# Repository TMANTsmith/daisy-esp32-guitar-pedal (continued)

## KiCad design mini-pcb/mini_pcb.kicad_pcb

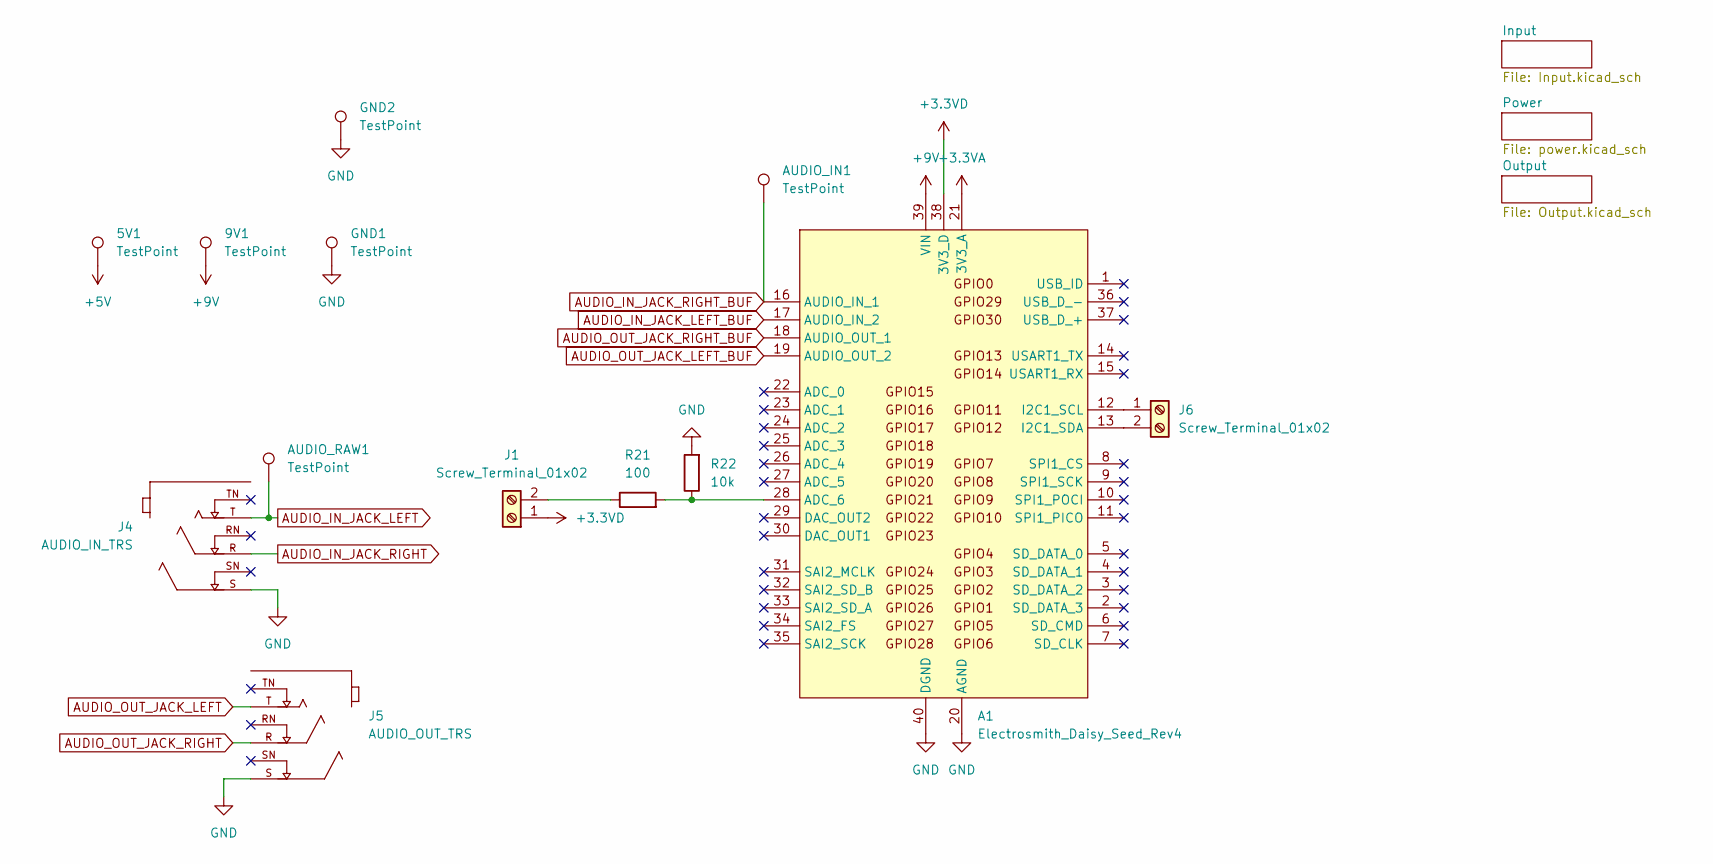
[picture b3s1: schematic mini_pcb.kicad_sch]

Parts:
5V1, 9V1: TestPoint; TestPoint_Pad_D2.0mm
A1: Electrosmith_Daisy_Seed_Rev4; Electrosmith_Daisy_Seed; MPN C50984
AUDIO_IN1: TestPoint; TestPoint_Pad_D2.0mm
AUDIO_RAW1: TestPoint; TestPoint_Pad_D2.0mm
GND1, GND2: TestPoint; TestPoint_Pad_D2.0mm
J1, J6: Screw_Terminal_01x02; TerminalBlock_Xinya_XY308-2.54-2P_1x02_P2.54mm_Horizontal; MPN C8465
J4: AUDIO_IN_TRS; Jack_6.35mm_Neutrik_NMJ6HCD3_Horizontal; PARTREV 26.02.2021
J5: AUDIO_OUT_TRS; Jack_6.35mm_Neutrik_NMJ6HCD3_Horizontal; PARTREV 26.02.2021
R21: 100; R_0603_1608Metric; MPN C22775
R22: 10k; R_0603_1608Metric; MPN C25804

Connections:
+3.3VA: A1.21 (3V3_A)
+3.3VD: A1.38 (3V3_D), J1.1
+5V: 5V1.1 (1_1); also elsewhere on the board
+9V: 9V1.1 (1_1), A1.39 (VIN); also elsewhere on the board
AUDIO_IN_JACK_LEFT: AUDIO_RAW1.1 (1_1), J4.T; also elsewhere on the board
AUDIO_IN_JACK_LEFT_BUF: A1.17 (AUDIO_IN_2); also elsewhere on the board
AUDIO_IN_JACK_RIGHT: J4.R; also elsewhere on the board
AUDIO_IN_JACK_RIGHT_BUF: A1.16 (AUDIO_IN_1), AUDIO_IN1.1 (1_1); also elsewhere on the board
AUDIO_OUT_JACK_LEFT: J5.T; also elsewhere on the board
AUDIO_OUT_JACK_LEFT_BUF: A1.19 (AUDIO_OUT_2); also elsewhere on the board
AUDIO_OUT_JACK_RIGHT: J5.R; also elsewhere on the board
AUDIO_OUT_JACK_RIGHT_BUF: A1.18 (AUDIO_OUT_1); also elsewhere on the board
GND: A1.20 (AGND), A1.40 (DGND), GND1.1 (1_1), GND2.1 (1_1), J4.S, J5.S, R22.2; also elsewhere on the board
unnamed: A1.28 (ADC_6), R21.2, R22.1
unnamed: A1.12 (I2C1_SCL), J6.1
unnamed: A1.13 (I2C1_SDA), J6.2
unnamed: J1.2, R21.1

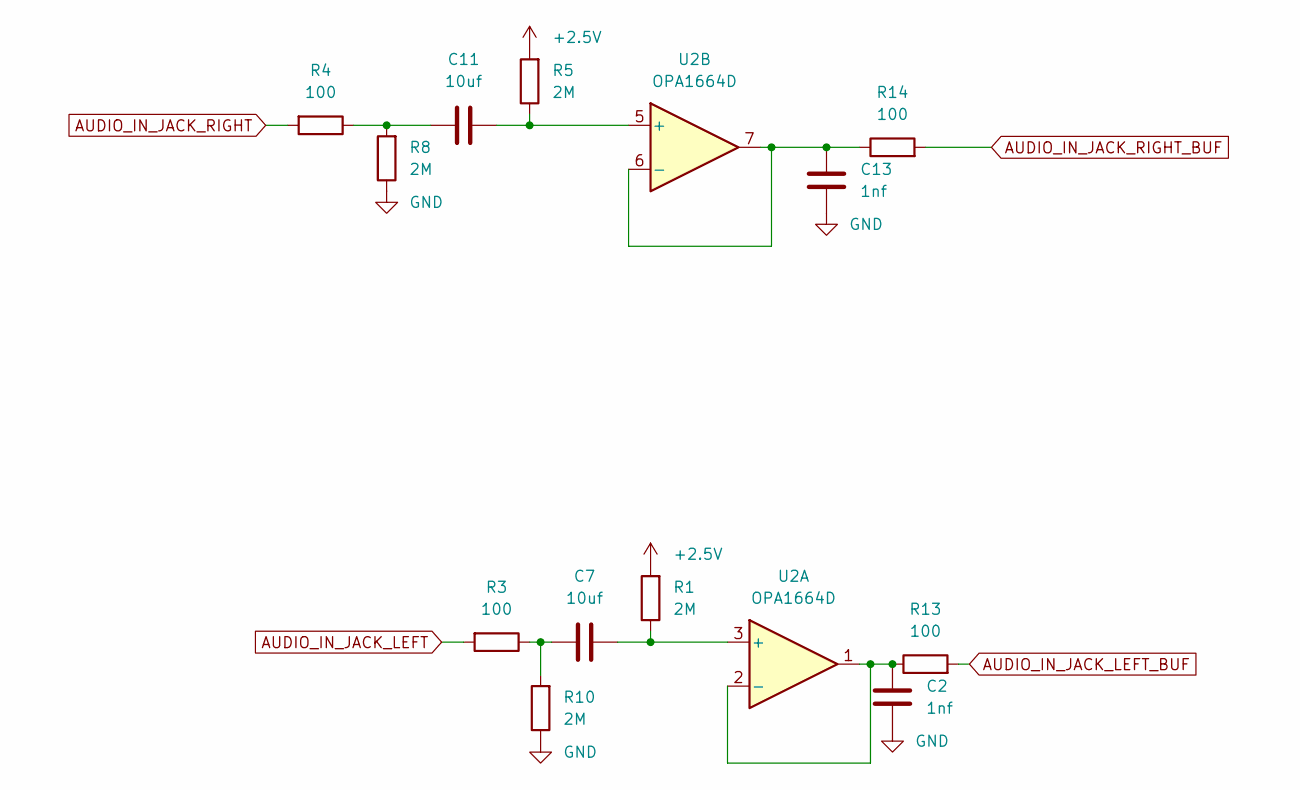
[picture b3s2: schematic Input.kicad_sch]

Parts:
C2, C13: 1nf; C_0805_2012Metric; MPN C46653
C7, C11: 10uf; C_0805_2012Metric; MPN C440198
R1, R5, R8, R10: 2M; R_0603_1608Metric; MPN C22976
R3, R4, R13, R14: 100; R_0603_1608Metric; MPN C22775
U2: OPA1664D; SOIC-14_3.9x8.7mm_P1.27mm; MPN C69414

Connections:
+2.5V: R1.2, R5.2; also elsewhere on the board
AUDIO_IN_JACK_LEFT: R3.2; also elsewhere on the board
AUDIO_IN_JACK_LEFT_BUF: R13.2; also elsewhere on the board
AUDIO_IN_JACK_RIGHT: R4.2; also elsewhere on the board
AUDIO_IN_JACK_RIGHT_BUF: R14.2; also elsewhere on the board
GND: C2.1, C13.1, R8.1, R10.1; also elsewhere on the board
unnamed: C7.1, R3.1, R10.2
unnamed: C11.1, R4.1, R8.2
unnamed: C7.2, R1.1, U2.3 (+)
unnamed: C2.2, R13.1, U2.1, U2.2 (-)
unnamed: C11.2, R5.1, U2.5 (+)
unnamed: C13.2, R14.1, U2.6 (-), U2.7

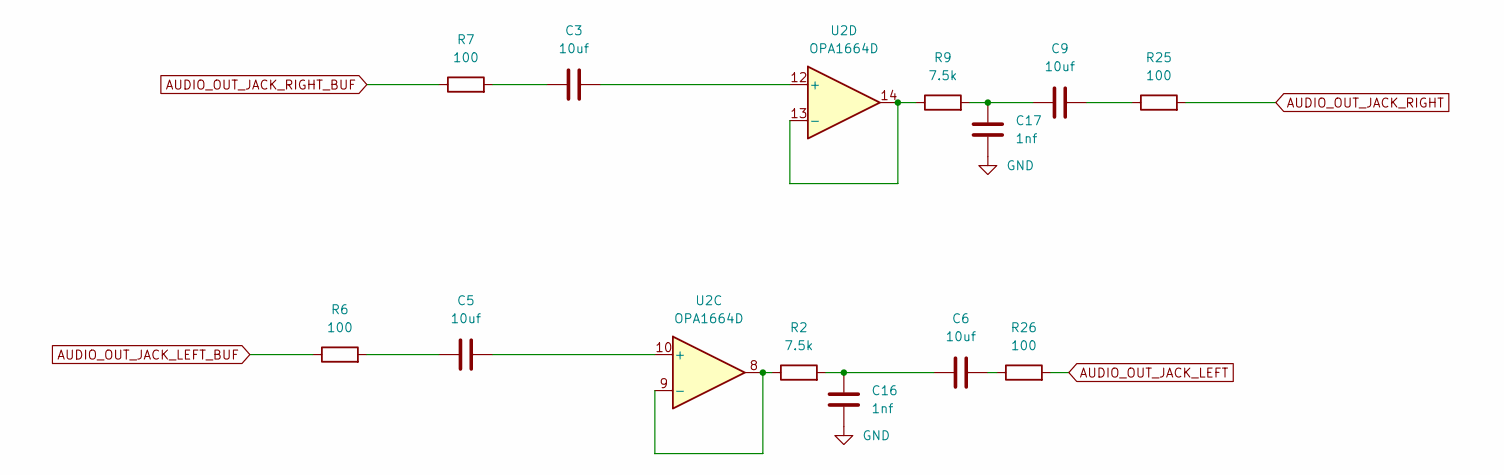
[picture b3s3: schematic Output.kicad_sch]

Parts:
C3, C5, C6, C9: 10uf; C_0805_2012Metric; MPN C440198
C16, C17: 1nf; C_0805_2012Metric; MPN C46653
R2, R9: 7.5k; R_0603_1608Metric; MPN C23234
R6, R7, R25, R26: 100; R_0603_1608Metric; MPN C22775
U2: OPA1664D; SOIC-14_3.9x8.7mm_P1.27mm; MPN C69414

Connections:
AUDIO_OUT_JACK_LEFT: R26.2; also elsewhere on the board
AUDIO_OUT_JACK_LEFT_BUF: R6.1; also elsewhere on the board
AUDIO_OUT_JACK_RIGHT: R25.2; also elsewhere on the board
AUDIO_OUT_JACK_RIGHT_BUF: R7.1; also elsewhere on the board
GND: C16.1, C17.1; also elsewhere on the board
unnamed: C3.1, R7.2
unnamed: C5.1, R6.2
unnamed: C6.2, R26.1
unnamed: C9.2, R25.1
unnamed: C6.1, C16.2, R2.2
unnamed: C9.1, C17.2, R9.2
unnamed: C5.2, U2.10 (+)
unnamed: R2.1, U2.8, U2.9 (-)
unnamed: C3.2, U2.12 (+)
unnamed: R9.1, U2.13 (-), U2.14

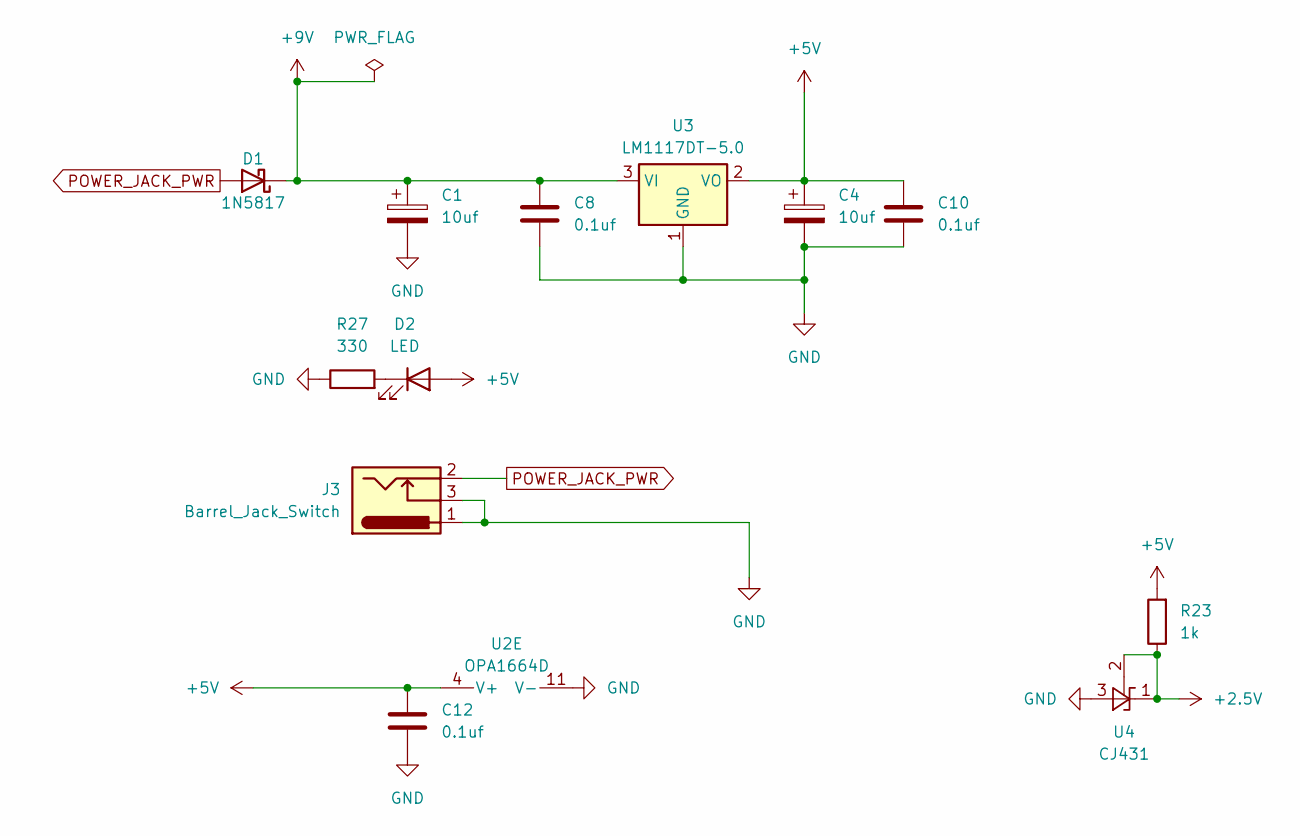
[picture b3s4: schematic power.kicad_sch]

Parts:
C1, C4: 10uf; CP_EIA-3216-18_Kemet-A; MPN C7171
C8, C10, C12: 0.1uf; C_0805_2012Metric; MPN C49678
D1: 1N5817; D_SOD-123; MPN C8598
D2: LED; LED_0805_2012Metric; MPN C2297
J3: Barrel_Jack_Switch; BarrelJack_Horizontal; MPN C16214
R23: 1k; R_0603_1608Metric; MPN C21190
R27: 330; R_0603_1608Metric; MPN C23138
U2: OPA1664D; SOIC-14_3.9x8.7mm_P1.27mm; MPN C69414
U3: LM1117DT-5.0; TO-252-2; MPN C354068
U4: CJ431; SOT-23-3; MPN C21190

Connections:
+2.5V: R23.1, U4.1 (FB), U4.2 (K); also elsewhere on the board
+5V: C4.1, C10.1, C12.1, D2.2 (A), R23.2, U2.4 (V+), U3.2 (VO); also elsewhere on the board
+9V: C1.1, C8.1, D1.1 (K), U3.3 (VI); also elsewhere on the board
GND: C1.2, C4.2, C8.2, C10.2, C12.2, J3.1, J3.3, R27.1, U2.11 (V-), U3.1 (GND), U4.3 (A); also elsewhere on the board
unnamed: D2.1 (K), R27.2
POWER_JACK_PWR: D1.2 (A), J3.2

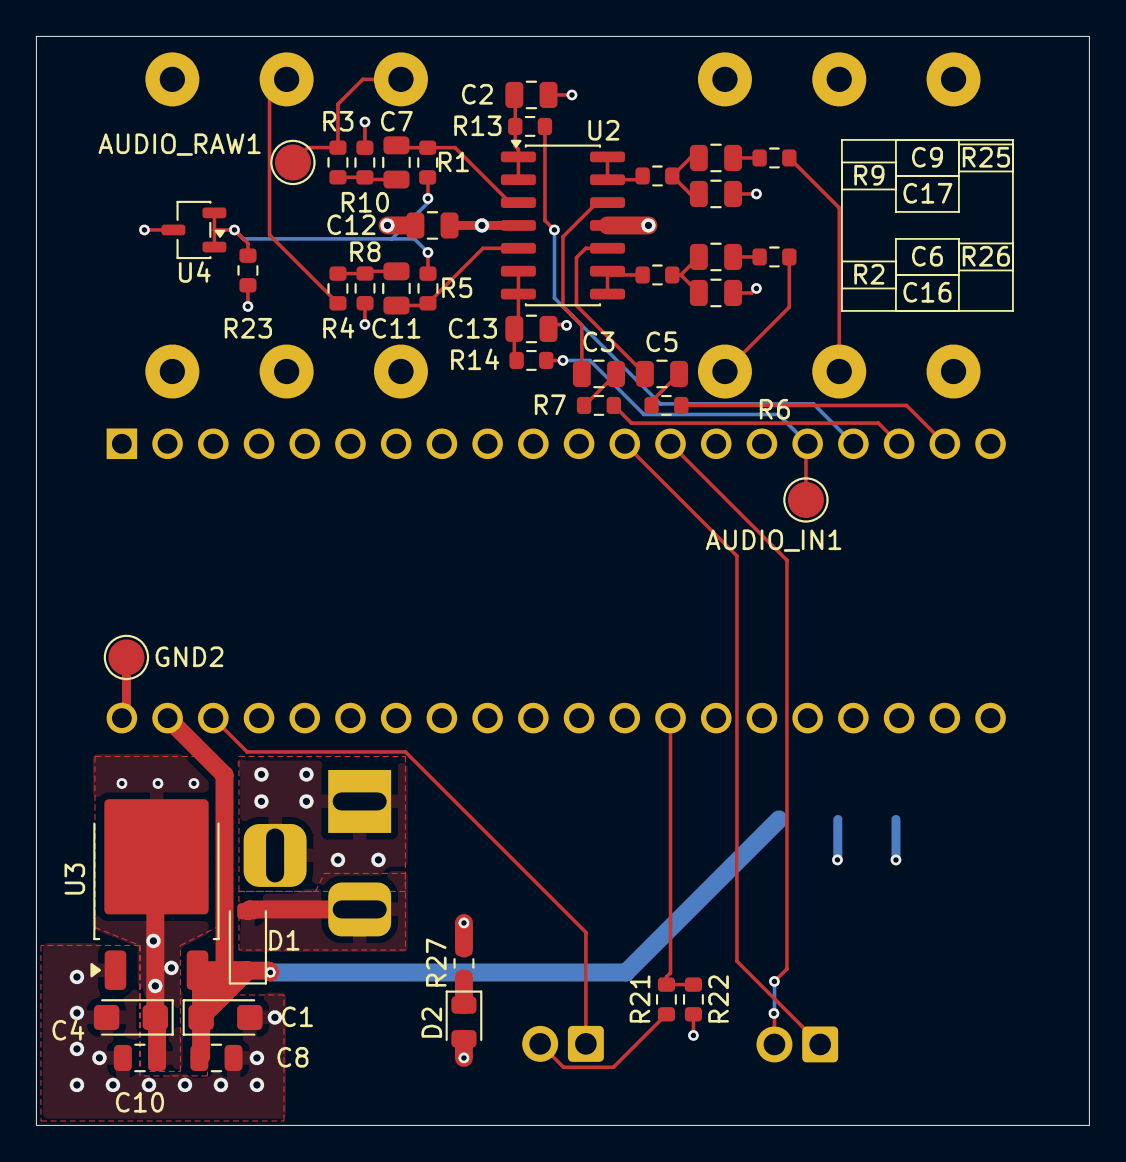
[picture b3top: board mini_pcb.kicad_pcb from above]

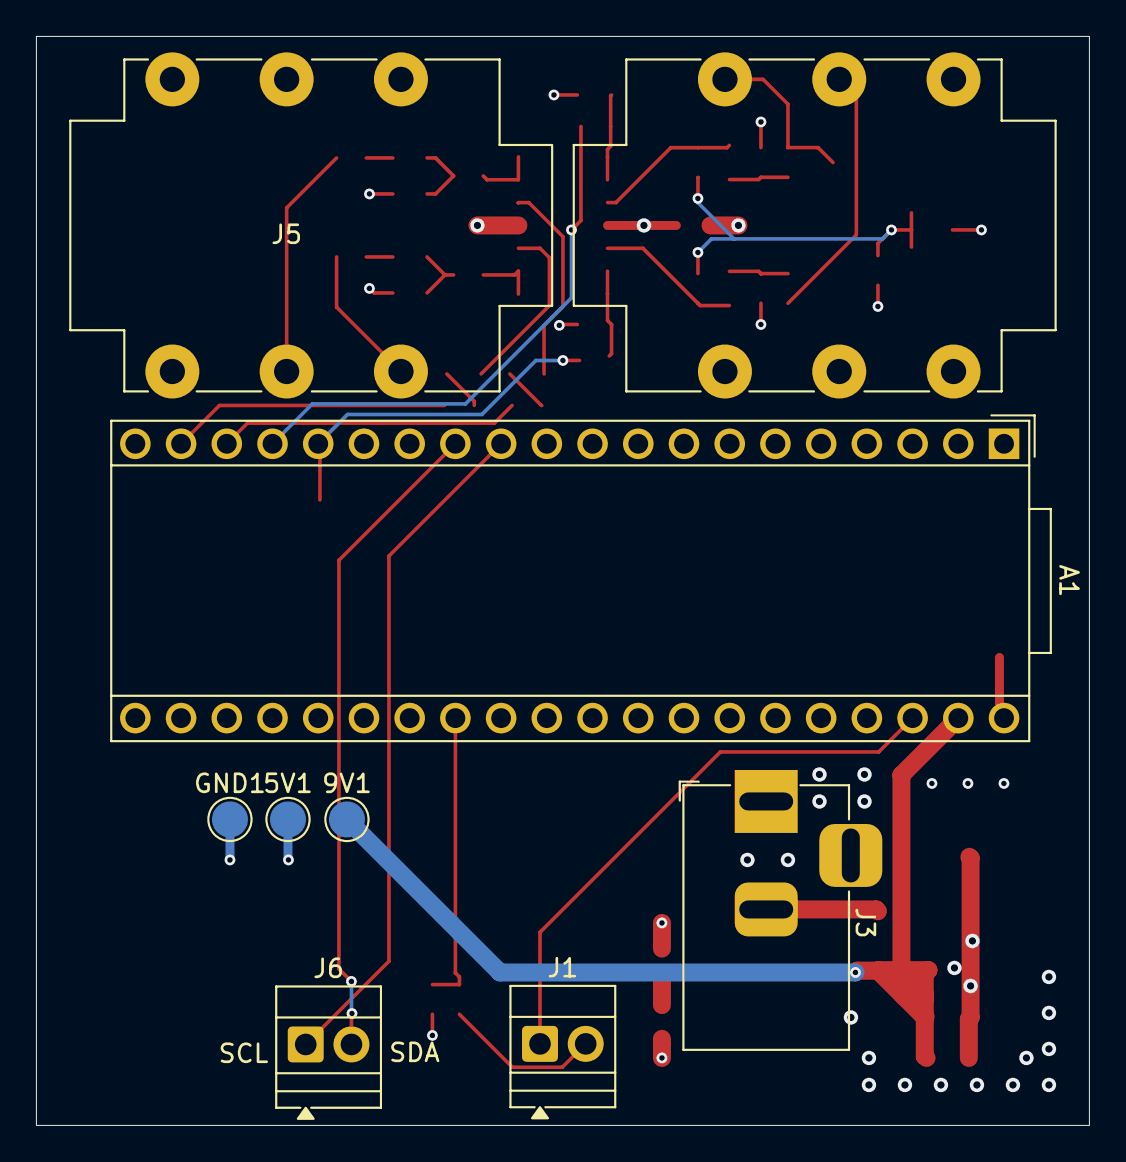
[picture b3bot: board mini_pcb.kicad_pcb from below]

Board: 4 copper layers, 58.5 x 60.5 mm, 50 parts (9 on the bottom side), 35 nets.

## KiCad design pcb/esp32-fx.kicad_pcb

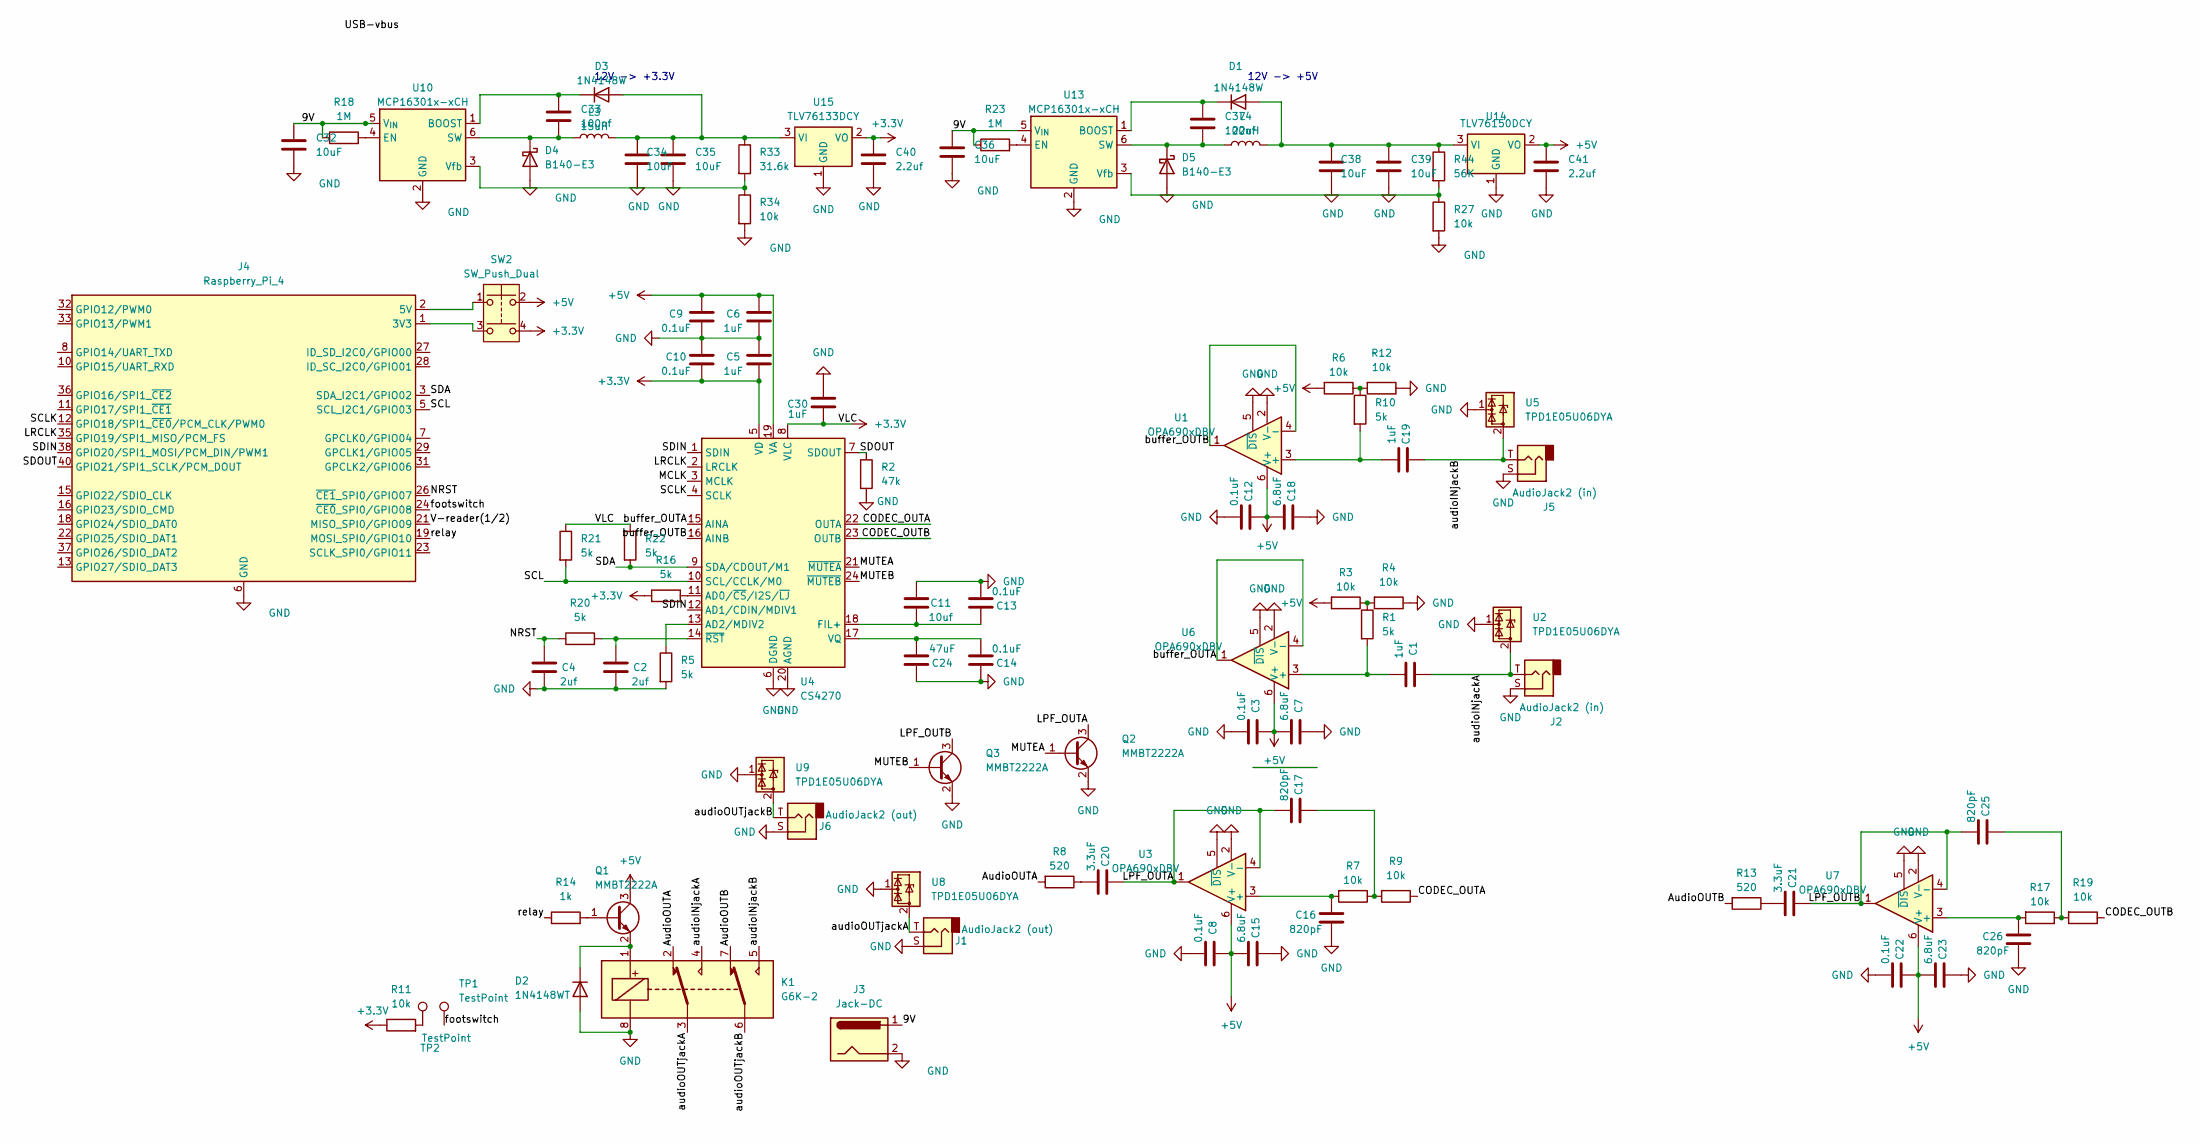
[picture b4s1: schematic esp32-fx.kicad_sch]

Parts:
C1, C5, C6, C19, C30: 1uF; C_0603_1608Metric
C2, C4: 2uf; C_0603_1608Metric
C3, C8, C9, C10, C12, C13, C14, C22: 0.1uF; C_0603_1608Metric
C7, C15, C18, C23: 6.8uF; C_0603_1608Metric
C11: 10uf; C_0603_1608Metric
C16, C17, C25, C26: 820pF; C_0603_1608Metric
C20, C21: 3.3uF; C_0603_1608Metric
C24: 47uF; C_0603_1608Metric
C32, C34, C35, C36, C38, C39: 10uF; C_0805_2012Metric
C33, C37: 100nf; C_0805_2012Metric
C40, C41: 2.2uf; C_0805_2012Metric
D1, D3: 1N4148W; D_SOD-523
D2: 1N4148WT; D_SOD-523
D4, D5: B140-E3; D_SMA
J1, J6: AudioJack2 (out); Jack_3.5mm_PJ320D_Horizontal
J2, J5: AudioJack2 (in); Jack_3.5mm_PJ320D_Horizontal
J3: Jack-DC; BarrelJack_SwitchcraftConxall_RAPC10U_Horizontal
J4: Raspberry_Pi_4; Raspberry_Pi_Zero_Socketed_THT_FaceDown_MountingHoles
K1: G6K-2; Relay_DPDT_Omron_G6K-2G
L3: 15uH; L_6.3x6.3_H3
L4: 22uH; L_6.3x6.3_H3
Q1, Q2, Q3: MMBT2222A; SOT-23
R1, R5, R10, R16, R20, R21, R22: 5k; R_0603_1608Metric
R2: 47k; R_0603_1608Metric
R3, R4, R6, R7, R9, R11, R12, R17, R19, R27, R34: 10k; R_0603_1608Metric
R8, R13: 520; R_0603_1608Metric
R14: 1k; R_0603_1608Metric
R18, R23: 1M; R_0603_1608Metric
R33: 31.6k; R_0603_1608Metric
R44: 56K; R_0603_1608Metric
SW2: SW_Push_Dual; SW_Push_1P1T_NO_CK_KMR2
TP1, TP2: TestPoint; TestPoint_Pad_D2.0mm
U1, U3, U6, U7: OPA690xDBV; SOT-23-6
U2, U5, U8, U9: TPD1E05U06DYA; D_SOD-523
U4: CS4270; TSSOP-24_4.4x7.8mm_P0.65mm
U10, U13: MCP16301x-xCH; SOT-23-6
U14: TLV76150DCY; SOT-223-3_TabPin2
U15: TLV76133DCY; SOT-223-3_TabPin2

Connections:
+3.3V: C5.1, C10.1, C30.1, C40.1, R11.1, R16.1, R21.1, R22.1, SW2.4, U4.5 (VD), U4.8 (VLC), U15.2 (VO)
+5V: C3.2, C6.2, C7.1, C8.2, C9.2, C12.2, C15.1, C18.1, C22.2, C23.1, C41.1, Q1.3 (C), R3.2, R6.2, SW2.2, U1.6 (V+), U3.6 (V+), U4.19 (VA), U6.6 (V+), U7.6 (V+), U14.2 (VO)
/9V: C32.1, C36.1, J3.1, R18.1, R23.1, U10.5 (V_{IN}), U13.5 (V_{IN})
/AudioOUTA: K1.2, R8.2
/AudioOUTB: K1.7, R13.2
/CODEC_OUTA: R9.1, U4.22 (OUTA)
/CODEC_OUTB: R19.1, U4.23 (OUTB)
/LPF_OUTA: C17.1, C20.2, Q2.3 (C), U3.1, U3.4 (-)
/LPF_OUTB: C21.2, C25.1, Q3.3 (C), U7.1, U7.4 (-)
/LRCLK: J4.35 (GPIO19/SPI1_MISO/PCM_FS), U4.2 (LRCLK)
/MCLK: U4.3 (MCLK)
/MUTEA: Q2.1 (B), U4.21 (~MUTEA)
/MUTEB: Q3.1 (B), U4.24 (~MUTEB)
/NRST: C4.2, J4.26 (~CE1_SPI0/GPIO07), R20.1
/SCL: J4.5 (SCL_I2C1/GPIO03), R21.2, U4.10 (SCL/CCLK/M0)
/SCLK: J4.12 (GPIO18/SPI1_~CE0/PCM_CLK/PWM0), U4.4 (SCLK)
/SDA: J4.3 (SDA_I2C1/GPIO02), R22.2, U4.9 (SDA/CDOUT/M1)
/SDIN: J4.38 (GPIO20/SPI1_MOSI/PCM_DIN/PWM1), U4.1 (SDIN), U4.12 (AD1/CDIN/MDIV1)
/SDOUT: J4.40 (GPIO21/SPI1_SCLK/PCM_DOUT), R2.1, U4.7 (SDOUT)
/V-reader(1/2): J4.21 (MISO_SPI0/GPIO09)
/audioINjackA: C1.2, J2.T, K1.4, U2.2 (GND)
/audioINjackB: C19.2, J5.T, K1.5, U5.2 (GND)
/audioOUTjackA: J1.T, K1.3, U8.2 (GND)
/audioOUTjackB: J6.T, K1.6, U9.2 (GND)
/buffer_OUTA: U4.15 (AINA), U6.1, U6.4 (-)
/buffer_OUTB: U1.1, U1.4 (-), U4.16 (AINB)
/footswitch: J4.24 (~CE0_SPI0/GPIO08), TP1.1
/relay: J4.19 (MOSI_SPI0/GPIO10), R14.1
GND: C2.1, C3.1, C4.1, C5.2, C6.1, C7.2, C8.1, C9.1, C10.2, C11.2, C12.1, C13.1, C14.2, C15.2, C16.1, C18.2, C22.1, C23.2, C24.2, C26.1, C30.2, C32.2, C34.2, C35.2, C36.2, C38.2, C39.2, C40.2, C41.2, D2.2 (A), D4.2 (A), D5.2 (A), J1.S, J2.S, J3.2, J4.6 (GND), J4.9 (GND), J4.14 (GND), J4.20 (GND), J4.25 (GND), J4.30 (GND), J4.34 (GND), J4.39 (GND), J5.S, J6.S, K1.8, Q2.2 (E), Q3.2 (E), R2.2, R4.1, R5.2, R12.1, R27.2, R34.2, U1.2 (V-), U1.5 (~DIS), U2.1 (I/O), U3.2 (V-), U3.5 (~DIS), U4.6 (DGND), U4.20 (AGND), U5.1 (I/O), U6.2 (V-), U6.5 (~DIS), U7.2 (V-), U7.5 (~DIS), U8.1 (I/O), U9.1 (I/O), U10.2 (GND), U13.2 (GND), U14.1 (GND), U15.1 (GND); also elsewhere on the board
unnamed: C17.2, R7.1, R9.2
unnamed: C20.1, R8.1
unnamed: C21.1, R13.1
unnamed: C25.2, R17.1, R19.2
unnamed: C38.1, C39.1, D1.2 (A), L4.2, R44.1, U14.3 (VI)
unnamed: C37.1, D1.1 (K), U13.1 (BOOST)
unnamed: D2.1 (K), K1.1, Q1.2 (E)
unnamed: C34.1, C35.1, D3.2 (A), L3.2, R33.1, U15.3 (VI)
unnamed: C33.1, D3.1 (K), U10.1 (BOOST)
unnamed: C33.2, D4.1 (K), L3.1, U10.6 (SW)
unnamed: C37.2, D5.1 (K), L4.1, U13.6 (SW)
unnamed: J4.1 (3V3), J4.17 (3V3), SW2.3
unnamed: J4.2 (5V), J4.4 (5V), SW2.1
unnamed: Q1.1 (B), R14.2
unnamed: R1.1, R3.1, R4.2
unnamed: R6.1, R10.1, R12.2
unnamed: R11.2, TP2.1
unnamed: C19.1, R10.2, U1.3 (+)
unnamed: C16.2, R7.2, U3.3 (+)
unnamed: R16.2, U4.11 (AD0/~CS/I2S/~LJ)
unnamed: R5.1, U4.13 (AD2/MDIV2)
unnamed: C11.1, C13.2, U4.18 (FIL+)
unnamed: C14.1, C24.1, U4.17 (VQ)
unnamed: C2.2, R20.2, U4.14 (~RST)
unnamed: C1.1, R1.2, U6.3 (+)
unnamed: C26.2, R17.2, U7.3 (+)
unnamed: R18.2, U10.4 (EN)
unnamed: R33.2, R34.1, U10.3 (Vfb)
unnamed: R23.2, U13.4 (EN)
unnamed: R27.1, R44.2, U13.3 (Vfb)

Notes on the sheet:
12V -> +3.3V
12V -> +5V

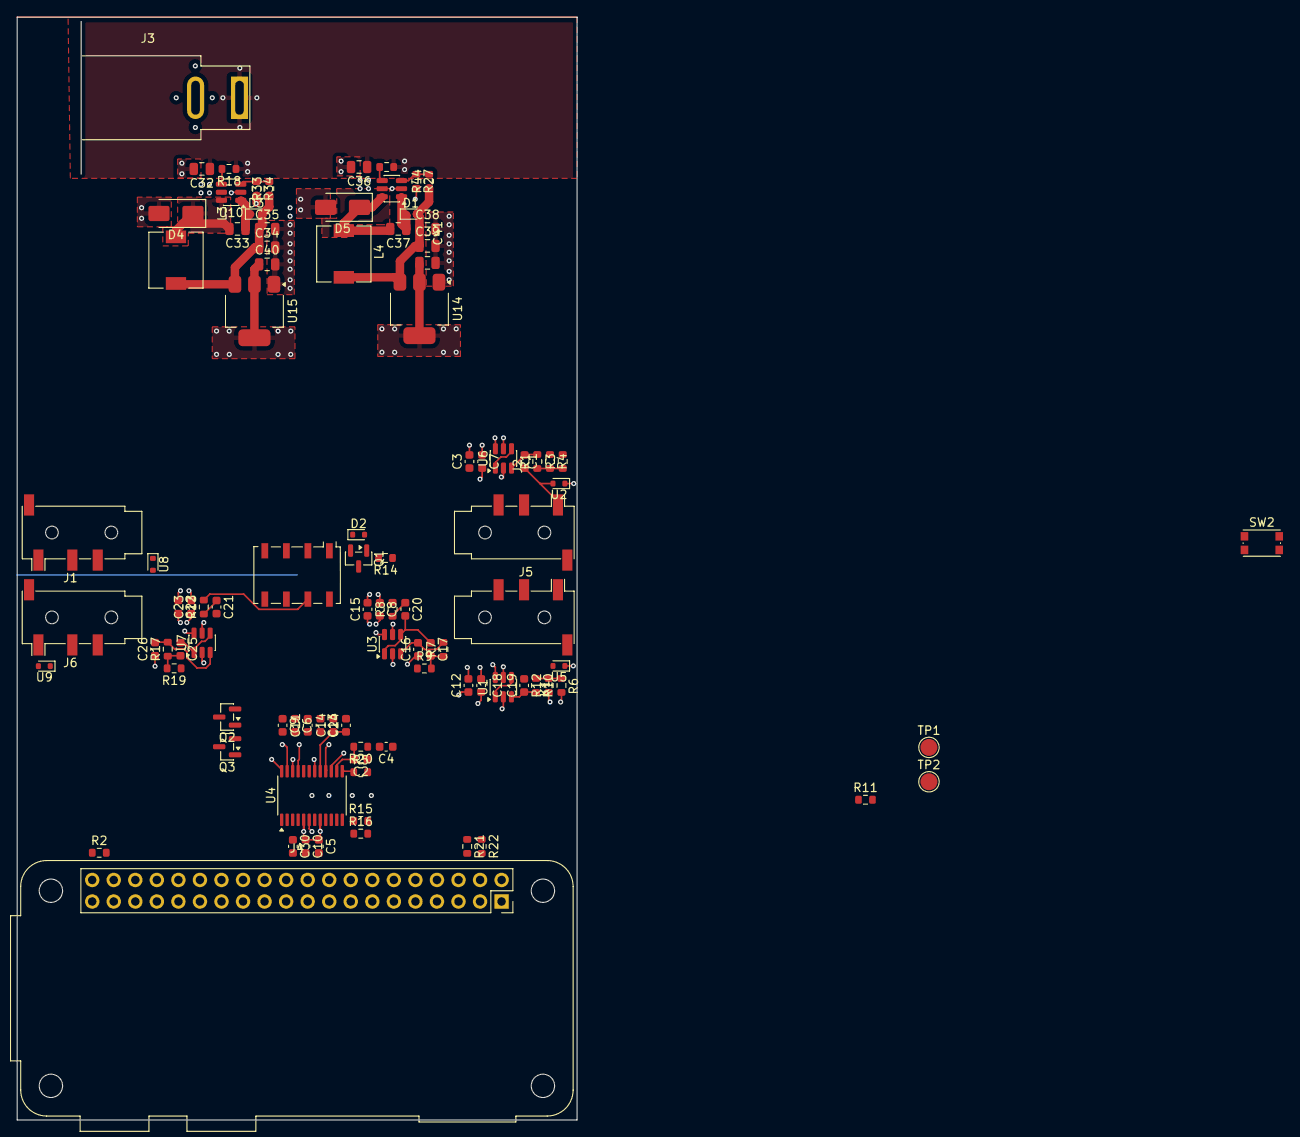
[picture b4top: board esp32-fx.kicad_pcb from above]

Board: 4 copper layers, 66.0 x 130.0 mm, 97 parts (0 on the bottom side), 57 nets.

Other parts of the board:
R15: 5k; R_0603_1608Metric

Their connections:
GND: R15.2; also elsewhere on the board

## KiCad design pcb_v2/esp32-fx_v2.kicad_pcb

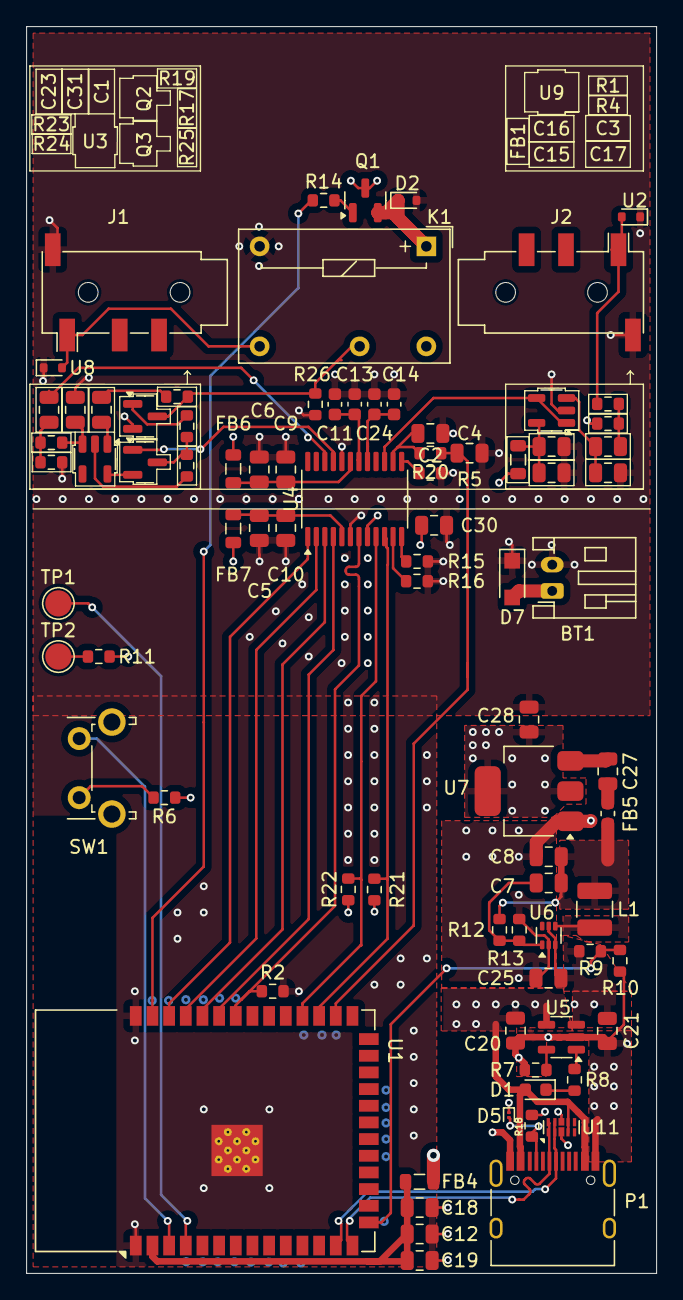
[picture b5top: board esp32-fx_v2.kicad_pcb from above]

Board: 4 copper layers, 48.0 x 95.0 mm, 84 parts (0 on the bottom side), 56 nets.

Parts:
BT1: Battery_Cell; JST_PH_S2B-PH-K_1x02_P2.00mm_Horizontal
C1, C5, C6, C16, C27, C30: 1uF; C_0805_2012Metric
C2, C4: 2uf; C_0805_2012Metric
C3: 10uf; C_0805_2012Metric
C7: 10pF; C_0805_2012Metric
C8: 22uF; C_0805_2012Metric
C9, C10, C15: 0.1uF; C_0805_2012Metric
C11: 10uf; C_0603_1608Metric
C12: 100nf; C_0805_2012Metric
C13, C14: 0.1uF; C_0603_1608Metric
C17: 220pf; C_0805_2012Metric
C18: 10nf; C_0805_2012Metric
C19: 1nf; C_0805_2012Metric
C20, C21: 4.7uF; C_0805_2012Metric
C23, C31: 3.3uf; C_0805_2012Metric
C24: 47uF; C_0603_1608Metric
C25: 10uF; C_0805_2012Metric
C28: 2.2uF; C_0805_2012Metric
D1: LED; LED_0603_1608Metric
D2: 1N4148WT; D_SOD-523
D5: ESD131-B1-W0201; Infineon_SG-WLL-2-3_0.58x0.28_P0.36mm
D7: PMEG3010BER; Nexperia_CFP3_SOD-123W
FB1, FB4, FB6, FB7: 100 Ω at 100 MHz; L_0805_2012Metric
FB5: FerriteBead; L_0603_1608Metric
J1: AudioJack2 (out); Jack_3.5mm_PJ320D_Horizontal
J2: AudioJack2 (in); Jack_3.5mm_PJ320D_Horizontal
K1: G6E-134P-US-DC3; Relay_SPDT_Omron_G6E
L1: 2.2uH; L_1210_3225Metric
P1: USB_C_Plug_USB2.0; USB_C_Receptacle_HRO_TYPE-C-31-M-12
Q1, Q2: MMBT2222A; SOT-23
Q3: MMUN2111LT1; SOT-23
R1, R4, R7, R17: 2k; R_0603_1608Metric
R2, R26: 47k; R_0603_1608Metric
R5, R15, R16, R20, R21, R22: 5k; R_0603_1608Metric
R6, R11, R24, R25: 10k; R_0603_1608Metric
R8, R14: 1k; R_0603_1608Metric
R9, R10: 100k; R_0603_1608Metric
R12: 100K; R_0603_1608Metric
R13: 20K; R_0603_1608Metric
R18: 5.1 kΩ; R_0603_1608Metric
R19: 560; R_0603_1608Metric
R23: 470; R_0603_1608Metric
SW1: SW_Push; SW_Tactile_SPST_Angled_PTS645Vx83-2LFS
TP1, TP2: TestPoint; TestPoint_Pad_D2.0mm
U1: ESP32-S3-WROOM-1
U2, U8: TPD1E05U06DYA; D_SOD-523
U3, U9: OPA333xxDBV; SOT-23-5
U4: CS4270; TSSOP-24_4.4x7.8mm_P0.65mm
U5: MCP73831-5-OT; SOT-23-5
U6: TLV62568ADRL; SOT-563
U7: TLV76133DCY; SOT-223-3_TabPin2
U11: D3V3XA4B10LP; Diodes_UDFN-10_1.0x2.5mm_P0.5mm

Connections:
+3.3V: C28.1, C30.1, FB1.1, FB4.1, FB6.1, FB7.1, Q1.3 (C), R6.1, R11.1, R21.1, R22.1, U4.8 (VLC), U7.2 (VO)
/AudioOUT: K1.10, Q2.3 (C), R19.2, R26.1
/BCLK: U1.35 (IO42), U4.4 (SCLK)
/DIN: R2.1, U1.34 (IO41), U4.7 (SDOUT)
/DOUT: U1.38 (IO2), U4.1 (SDIN)
/D_N: P1.A7 (D-), U1.13 (USB_D-), U11.2, U11.9 (NC)
/D_P: P1.A6 (D+), U1.14 (USB_D+), U11.1, U11.10 (NC)
/LPF: C31.2, R23.2, U3.3 (+)
/LRCKL: U1.37 (TXD0), U4.2 (LRCLK)
/MCLK: U1.36 (RXD0), U4.3 (MCLK)
/MUTE: Q3.1 (B), U4.21 (~MUTEA)
/MUTE+: Q3.2 (E), U3.5 (V+)
/MUTE-: R25.1, U3.2 (V-)
/NRST: C4.2, R20.1, U1.28 (IO35)
/On-button: SW1.2, U1.3 (EN)
/SCL: R21.2, U1.29 (IO36), U4.10 (SCL/CCLK/M0)
/SDA: R22.2, U1.30 (IO37), U4.9 (SDA/CDOUT/M1)
/U3A-OUT: U4.15 (AINA), U9.1, U9.4 (-)
/USB-vbus: C20.2, D1.2 (A), P1.A4 (VBUS), P1.A9 (VBUS), P1.B4 (VBUS), P1.B9 (VBUS), U5.4 (V_{DD}), U11.4, U11.7 (NC)
/V-reader(1/2): R9.1, R10.1, U1.15 (IO3)
/audioOUTjack: J1.T, K1.7, U8.2 (GND)
/footswitch: TP1.1, U1.4 (IO4)
/relay: R14.1, U1.39 (IO1)
GND: BT1.2 (-), C2.1, C4.1, C5.2, C6.1, C8.2, C9.1, C10.2, C11.2, C12.2, C13.1, C14.2, C15.2, C16.2, C17.1, C18.2, C19.2, C20.1, C21.1, C24.2, C25.2, C27.1, C28.2, C30.2, C31.1, D2.2 (A), D5.1 (A1), D7.1 (K), J1.S, J2.S, K1.6, P1.A1 (GND), P1.A12 (GND), P1.B1 (GND), P1.B12 (GND), Q2.2 (E), R2.2, R4.2, R5.2, R7.1, R10.2, R13.2, R15.2, R16.2, R18.2, R24.1, R26.2, U1.1 (GND), U1.40 (GND), U1.41 (GND), U2.1 (I/O), U4.6 (DGND), U4.20 (AGND), U5.2 (V_{SS}), U6.2 (GND), U7.1 (GND), U8.1 (I/O), U9.2 (V-), U11.3 (VSS), U11.8 (VSS)
unnamed: BT1.1 (+), C21.2, C25.1, D7.2 (A), R9.2, U5.3 (V_{BAT}), U6.3 (VIN), U6.5 (EN)
unnamed: C1.1, U3.1
unnamed: C1.2, R19.1
unnamed: C3.2, R1.1, R4.1
unnamed: C7.1, C8.1, FB5.1, L1.2, R12.1
unnamed: C23.2, R23.1, R24.2
unnamed: D1.1 (K), R8.2
unnamed: D2.1 (K), K1.1, Q1.2 (E)
unnamed: D5.2 (A2), P1.A5 (CC), R18.1
unnamed: Q1.1 (B), R14.2
unnamed: Q2.1 (B), R17.2
unnamed: Q3.3 (C), R17.1, R25.2
unnamed: R6.2, SW1.1
unnamed: R11.2, TP2.1
unnamed: C12.1, C18.1, C19.1, FB4.2, U1.2 (3V3)
unnamed: J2.T, R1.2, U2.2 (GND)
unnamed: R16.1, U4.11 (AD0/~CS/I2S/~LJ)
unnamed: R15.1, U4.12 (AD1/CDIN/MDIV1)
unnamed: R5.1, U4.13 (AD2/MDIV2)
unnamed: C11.1, C13.2, U4.18 (FIL+)
unnamed: C23.1, U4.22 (OUTA)
unnamed: C6.2, C9.2, FB6.2, U4.19 (VA)
unnamed: C5.1, C10.1, FB7.2, U4.5 (VD)
unnamed: C14.1, C24.1, U4.17 (VQ)
unnamed: C2.2, R20.2, U4.14 (~RST)
unnamed: R7.2, U5.5 (PROG)
unnamed: R8.1, U5.1 (STAT)
unnamed: C7.2, R12.2, R13.1, U6.1 (FB)
unnamed: L1.1, U6.4 (SW)
unnamed: C27.2, FB5.2, U7.3 (VI)
unnamed: C3.1, C17.2, U9.3 (+)
unnamed: C15.1, C16.1, FB1.2, U9.5 (V+)

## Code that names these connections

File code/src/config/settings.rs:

pub const relay : u8 = 1;

pub const footswitch : u8 = 4;

pub const vreader : u8 = 3;


pub const d_n : u8 = 19;
pub const d_p : u8 = 20;

// CODEC related below //

pub const I2S_SCL : u8 = 36;
pub const I2S_SDA : u8 = 37;

pub const I2C_DOUT: u8 = 2;
pub const I2C_DIN : u8 = 41;
pub const I2C_BLCK : u8 = 42;
pub const I2C_LRCK : u8 = 43;
pub const I2C_MCLK : u8 = 44;

pub const nrst : u8 = 35;

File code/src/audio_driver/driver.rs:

use crate::config::settings;
use esp_idf_hal::prelude::*;  // Brings in useful helpers like Hz units
use esp_idf_hal::i2c::*;      // I2C driver and config
use esp_idf_hal::peripherals::Peripherals; // Access ESP32 peripherals
use esp_idf_hal::i2s::*;
use esp_idf_hal::gpio::GpioPin;

// Define a struct to hold the state of the audio driver
pub struct AudioDriver {
    i2c: Master<'static>, // 'Master' is the I2C master peripheral
                          // 'static lifetime means it lives for the program's lifetime
                          // This stores the I2C object so it can be used in methods
}

// Implement methods for the AudioDriver struct
impl AudioDriver {
    // Constructor for AudioDriver
    // Returns Result<Self> because initializing I2C can fail
    // 'Self' here refers to the struct AudioDriver itself
    pub fn new() -> anyhow::Result<Self> {
        // Take ownership of ESP32 peripherals
        let peripherals = Peripherals::take().unwrap();

        // Configure GPIO pins for SDA and SCL from settings
        let sda = peripherals.pins.gpio(settings::I2C_SDA);
        let scl = peripherals.pins.gpio(settings::I2C_SCL);

        // Configure I2C parameters: set baud rate from settings
        let config = MasterConfig::new().baudrate(settings::100.kHz().into());

        // Initialize the I2C peripheral
        // The '?' operator propagates errors as an anyhow::Error
        let i2c = Master::new(peripherals.i2c0, sda, scl, &config)?;

        // Return an instance of AudioDriver wrapped in Ok()
        // Ok() means this function succeeded and provides the value
        Ok(Self { i2c })
    }

    // Method to write bytes to a device at a given I2C address
    // Returns Result<()> to indicate success or failure
    pub fn write(&mut self, addr: u8, data: &[u8]) -> anyhow::Result<()> {
        self.i2c.write(addr, data)?; // Send bytes via I2C; propagate error if it fails
        Ok(()) // Return Ok with unit type () meaning "success with no value"
    }

    // Method to read bytes from a device at a given I2C address
    // Returns Result<()> for error handling
    pub fn read(&mut self, addr: u8, buffer: &mut [u8]) -> anyhow::Result<()> {
        self.i2c.read(addr, buffer)?; // Read bytes into buffer; propagate error if it fails
        Ok(()) // Indicate success
    }
    pub fn mwrite(&mut self, addr: u8, bit : u8, value : bool) -> anyhow::Result<()> {
        let mut current: [u8; 1] = [0];
        audio_driver.read(DEVICE_ADDRESS, &mut current)?;

        if value == True {
            current[0] |= 1 << bit;
        } else {
            current[0] &= !(1 << bit);
        }
        audio_driver.write(DEVICE_ADDRESS, &[addr, current[0]])?;
        Ok(())
    }

        

// ---------- I2S stuff  ---------- //

pub fn init_i2s() -> anyhow::Result<I2sDriver<'static>> {
    // 1️⃣ Configure I2S driver
    let config = I2sDriverConfig::new()
        .sample_rate(44_100)                     // LRCLK = 44.1 kHz
        .data_bits(DataBits::Bits24)            // 24-bit samples
        .channel_format(ChannelFormat::Mono)    // Mono audio
        .communication_format(CommunicationFormat::I2S)
        .dma_buf_count(8)
        .dma_buf_len(256)
        .mode(I2sMode::Master);                 // ESP32 drives all clocks

    let i2s = I2sDriver::new(
        I2sNum::I2S0,
        BckPin::new(I2S_BLCK),   // Choose your BCLK pin
        WsPin::new(I2S_LRCK),    // TXD0 → LRCLK
        DataOutPin::new(I2S_DOUT),
        Some(DataInPin::new(I2S_DIN)),
        config,
    )?;

    unsafe {
        let pins = i2s_pin_config_t {
            mclk_out_num: gpio_num_t_GPIO_NUM_44, // RXD0 → MCLK
            bck_io_num: I2S_BLCK,                 // BCLK
            ws_io_num: I2S_LRCK,                  // LRCLK → TXD0
            data_out_num: I2S_DOUT,
            data_in_num: I2S_DIN,
        };
        i2s_set_pin(i2s_port_t_I2S_NUM_0, &pins);

        i2s_set_clk(
            i2s_port_t_I2S_NUM_0,
            44_100,                                         // sample rate
            i2s_bits_per_sample_t_I2S_BITS_PER_SAMPLE_24BIT,
            i2s_channel_t_I2S_CHANNEL_MONO,
        );
    }

    Ok(i2s)
}

pub fn unpack(in_bytes: &[u8]) -> Vec<f32> {
    let mut out_samples = Vec::with_capacity(in_bytes.len() / 3);
    for chunk in in_bytes.chunks_exact(3) {
        let raw = ((chunk[0] as u32) << 16)
                | ((chunk[1] as u32) << 8)
                | (chunk[2] as u32);
        let sample_i32 = (raw << 8) as i32 >> 8;
        let f = sample_i32 as f32 / (1 << 23) as f32;
        out_samples.push(f);
    }
    out_samples
}

pub fn pack(in_samples: &[f32]) -> Vec<u8> {
    let mut out_bytes = Vec::with_capacity(in_samples.len() * 3);
    for &f in in_samples {
        // scale back to 24-bit integer range
        let s = (f * (1 << 23) as f32).clamp(-(1 << 23) as f32, (1 << 23) as f32 - 1.0) as i32;
        out_bytes.push(((s >> 16) & 0xFF) as u8);
        out_bytes.push(((s >> 8) & 0xFF) as u8);
        out_bytes.push((s & 0xFF) as u8);
    }
    out_bytes
}
